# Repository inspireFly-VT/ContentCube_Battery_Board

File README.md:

View this project on [CADLAB.io](https://cadlab.io/project/28565). 

# battery_board
The battery and power management board for the PROVES Kit.
# Flight Heritage
| Version | Flights | Status |
| ----------- | ----------- | ----------- |
| V0 | Unflown | Not Supported |
| V1 | Unflown | Not Supported |
| V2 | Pleiades - Yearling, Pleaides - Squared | Supported |
| V3 | Planned Pleiades - Orpheus | In Development |
# Features
## battery_board_v2
The battery board flown on the Pleiades-Yearling and Pleiades-Squared missions. The board serves as an interface with the rest of the satellite. A 12 position picolock is utilized to interface between the Flight Controller and the Battery Board. The board interfaces with 5 solar faces of the satellite using 5 position picolocks. The other 2 position picolocks are used for interfacing with the inhibit scheme, battery heater, burn wire, and direct charging port. The hardware utilized on the module is the following:
- **LT3652 MPPT Solar Charger** is utilized to charge the batteries up from the solar faces. The Solar Charging circuitry should only allow higher potentials to be fed to the battery, and allow no reverse current into the charging circuitry.
- **PCA9685 LED Driver** is utilized to toggle the power to each of the solar faces. In the event that a sensor or other component fails on a face, it makes it possible to isolate the problem and power down the face.
- **TCA9548 I2C Multiplexer** is implemented to allow the use of a single I2C bus from the flight computer. This I2C bus can then get multiplexed to the solar faces. This allows the sensors on all of the faces to be the exact same, maintain the same addresses, and still be individually addressable. Two of the multiplexed lines are unused, 5 are used for each solar face, and 1 is used to breakout a stemma QT connection for additional sensors or I2C devices.
- **TPS54226PWP Switching Voltage Regulator** is utilized to maximize the efficiency of the system, and generate less heat central to the system. A 3.3V bus is created from the battery voltage and circuitry inspired by the PyCubed has been implemented to allow the satellite to reset the 3.3V bus. This functionality is known as the "One Shot" Regulator Reset that with a logic "High" applied, the 3.3V bus will shutdown and restart momentarily.
- **TPS7A4501 LDO Voltage Regulator** is implemented to supply 5V to the radio on the flight controller. This bus voltage can be toggled by an input taken from the flight controller.
- **(2) INA219 Power Monitors** are implemented to measure the power supplied from the solar cells, and the power dropped across the system. This data is fed back via the I2C bus to the flight controller
- **PTC2075 Temperature Sensor** is utilized to obtain ambient temperature readings from inside the satellite.
- **R5460N208AA** is utilized to disconnect the negative side of the batteries from the system in overcharge and overdischarge events.
- **APAN3109 Relay** is implemented to allow current to flow to the battery heater and burn wire MOSFETS.

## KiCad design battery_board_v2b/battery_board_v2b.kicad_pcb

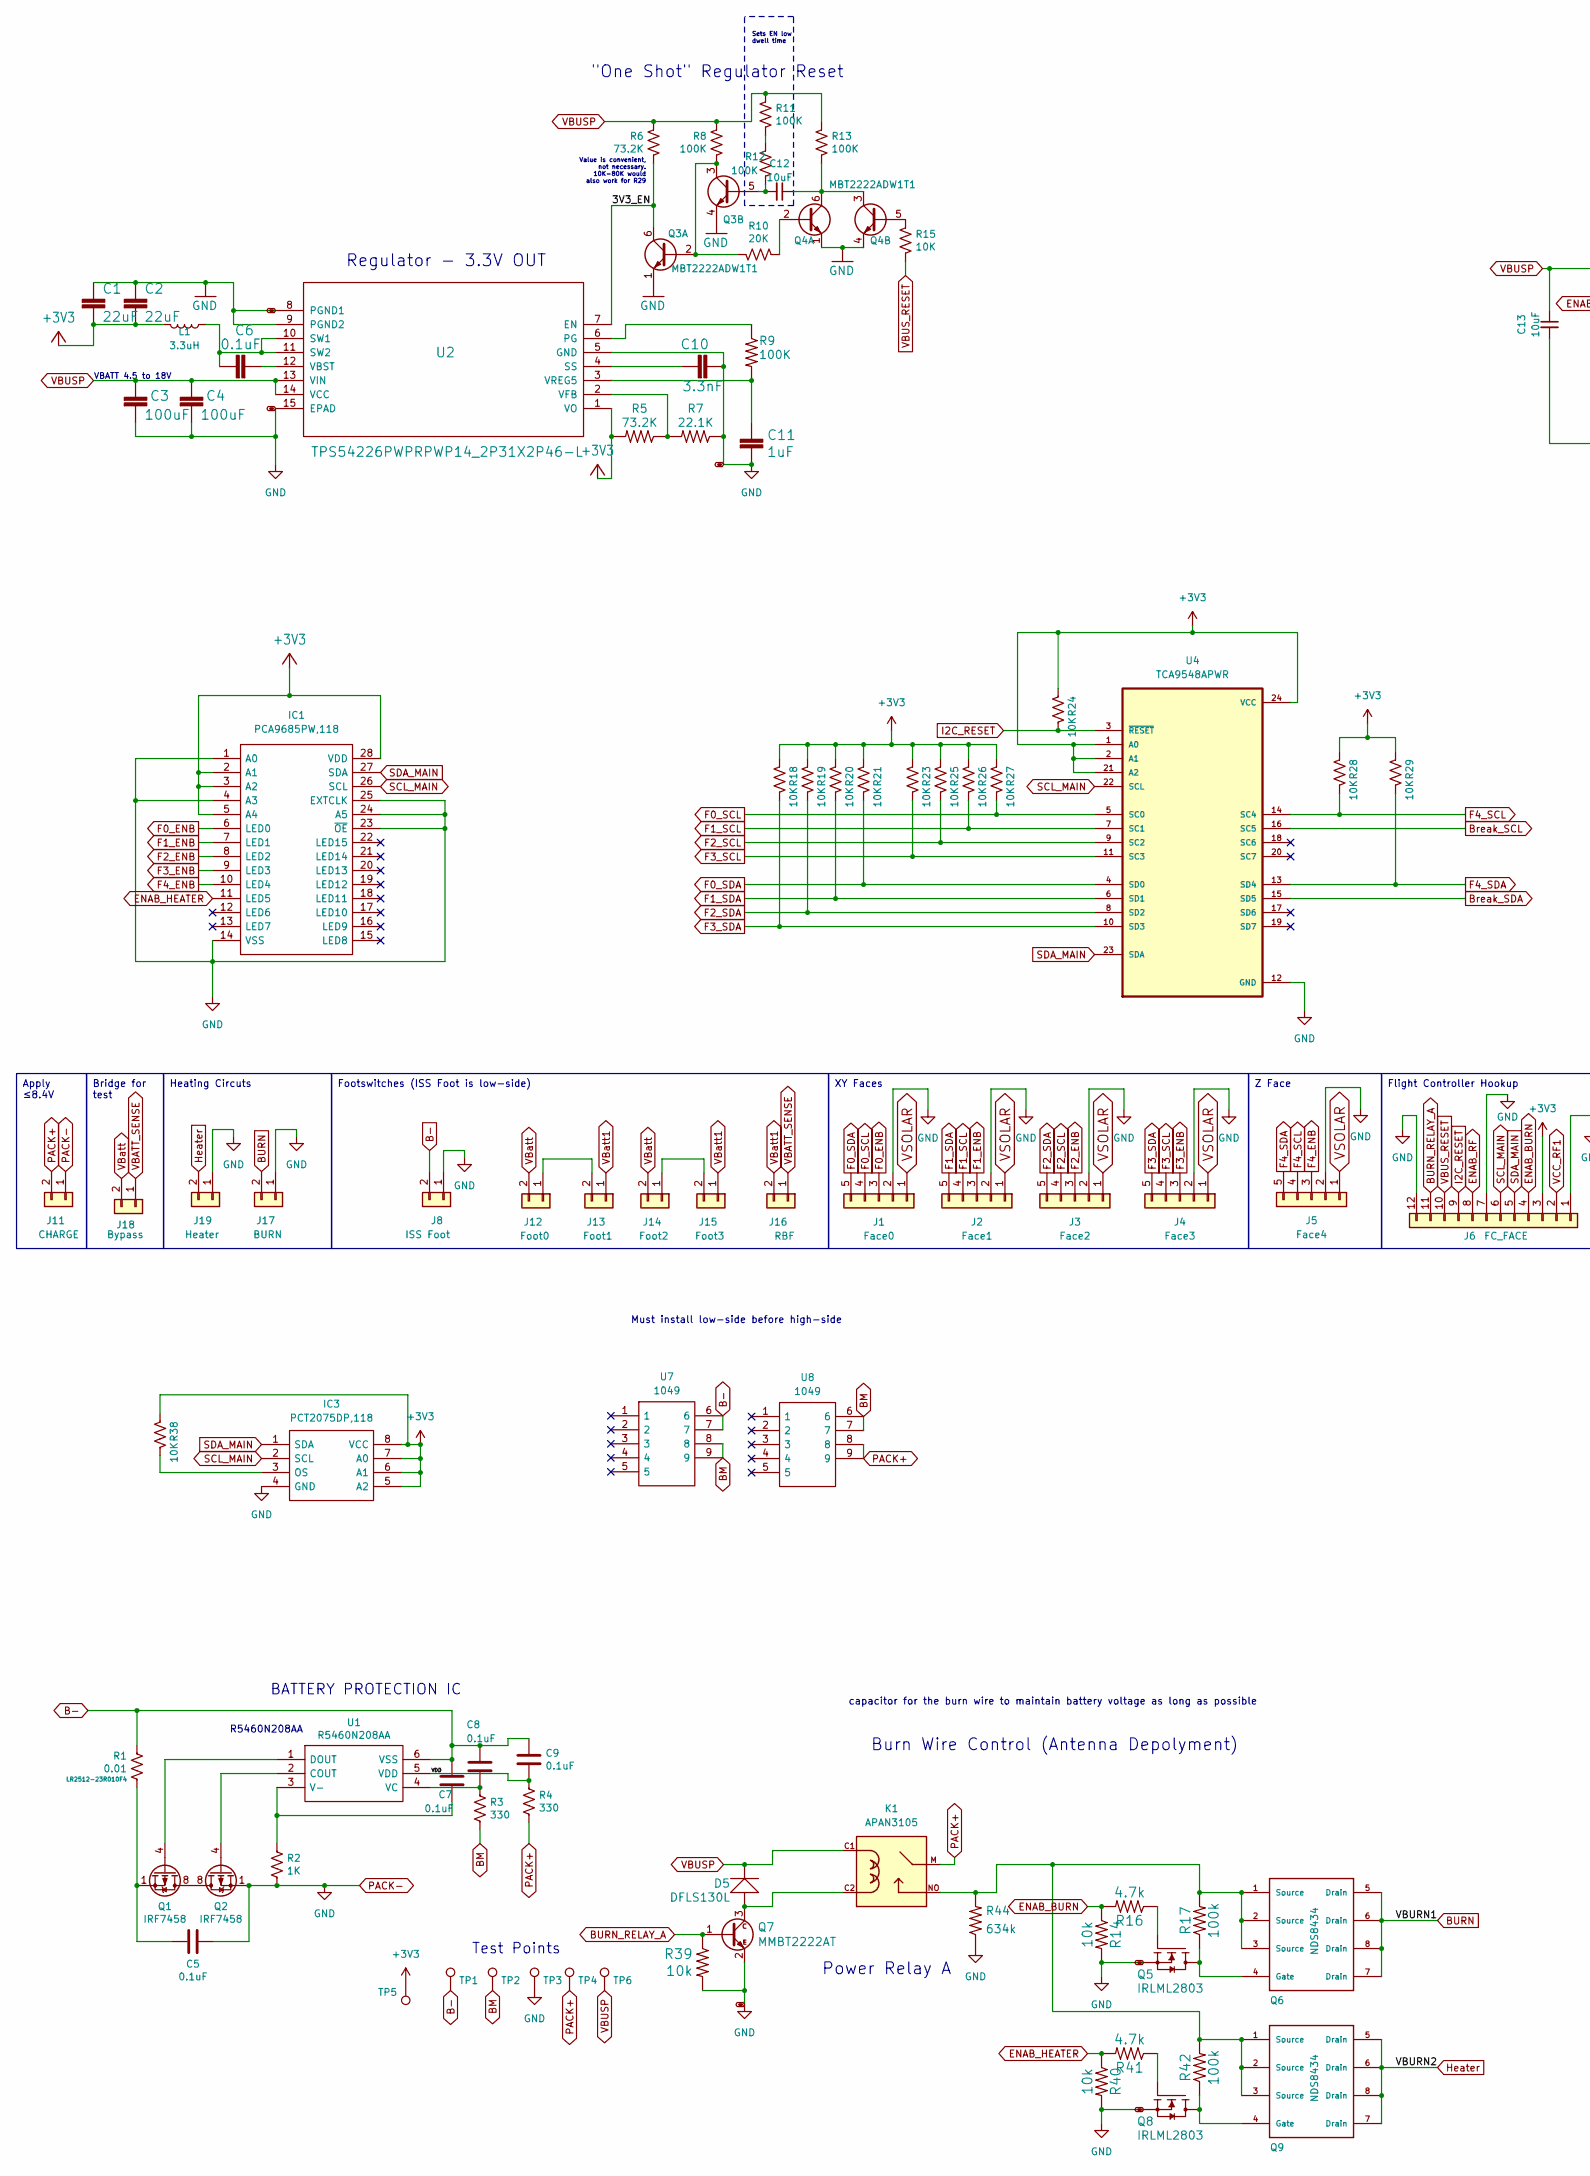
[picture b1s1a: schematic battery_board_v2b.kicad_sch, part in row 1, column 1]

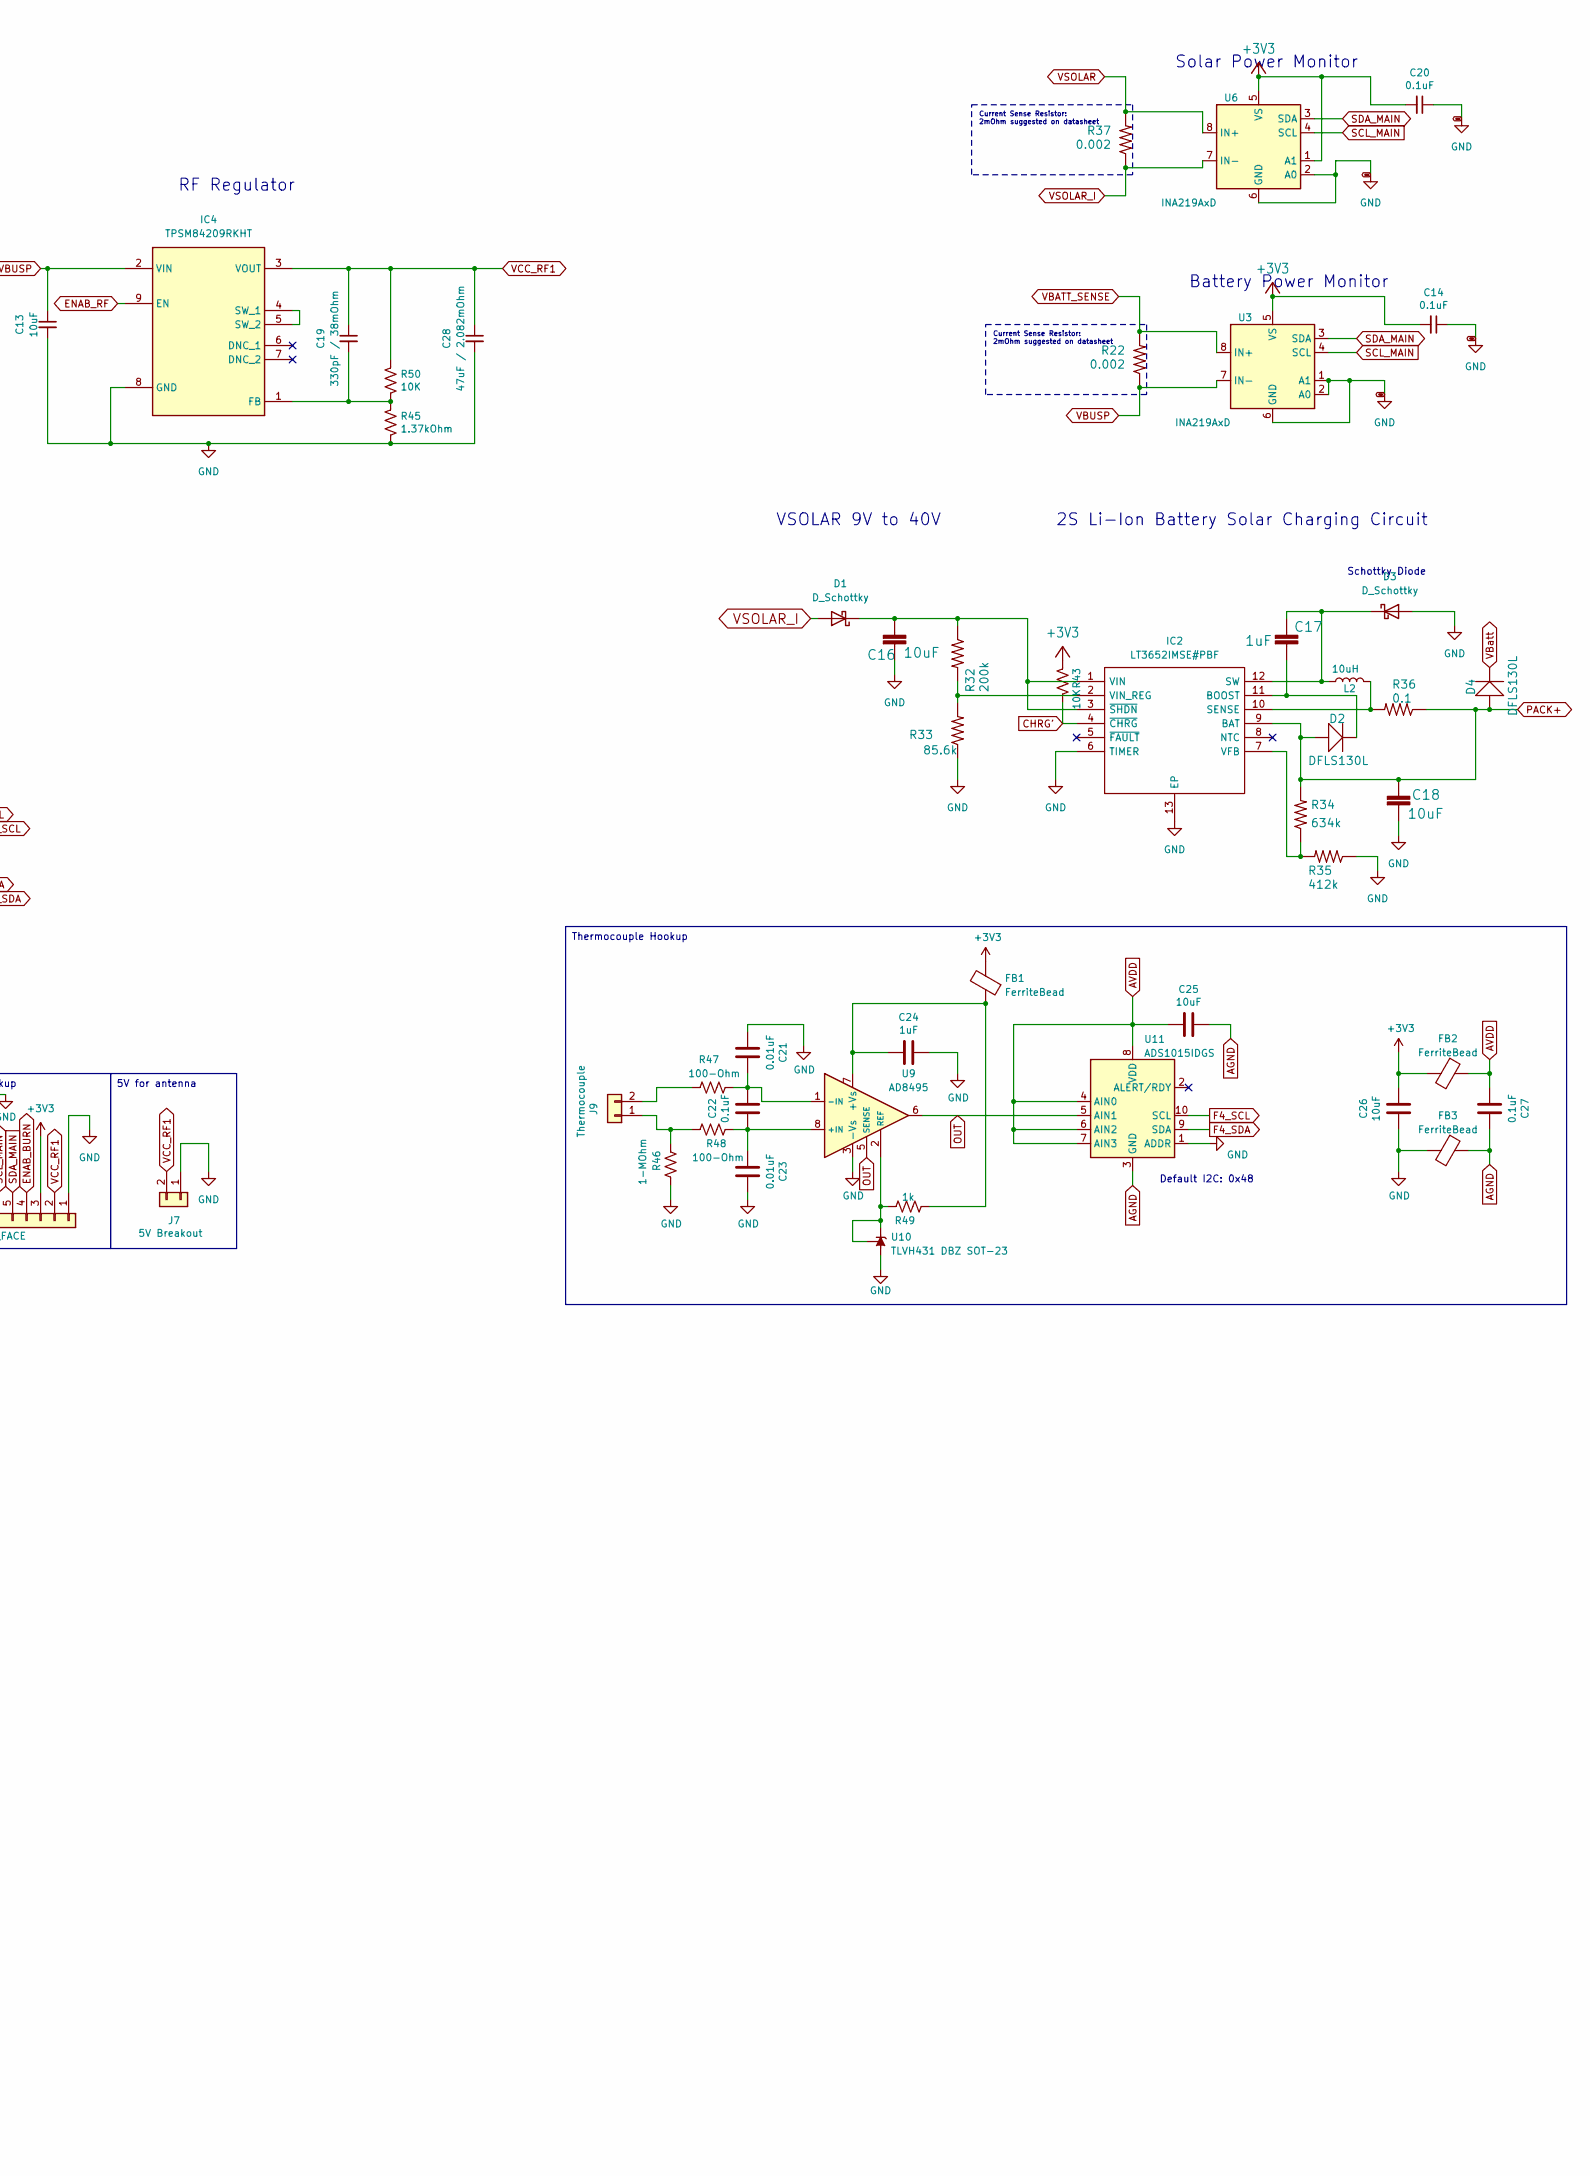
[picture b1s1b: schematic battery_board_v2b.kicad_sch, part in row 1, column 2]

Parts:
C1, C2: 22uF; C_0603_1608Metric
C3, C4: 100uF; C_1210_3225Metric
C5, C6, C7, C8, C9, C14, C20: 0.1uF; C_0603_1608Metric
C10: 3.3nF; C_0603_1608Metric
C11, C17: 1uF; C_0603_1608Metric
C12, C13, C16, C18: 10uF; C_0603_1608Metric
C19: 330pF / 38mOhm; C_0603_1608Metric
C21, C23: 0.01uF; C_0402_1005Metric_Pad0.74x0.62mm_HandSolder
C22, C27: 0.1uF; C_0402_1005Metric_Pad0.74x0.62mm_HandSolder
C24: 1uF; C_0402_1005Metric_Pad0.74x0.62mm_HandSolder
C25, C26: 10uF; C_0402_1005Metric_Pad0.74x0.62mm_HandSolder
C28: 47uF / 2.082mOhm; C_0603_1608Metric
D1, D3: D_Schottky; DIOM5226X262N
D2, D4, D5: DFLS130L; PWRDI-123; Manufacturer_Part_Number DFLS130L-7
FB1, FB2, FB3: FerriteBead; R_0603_1608Metric
IC1: PCA9685PW,118; SOP65P640X110-28N; Mouser Part Number 771-PCA9685PW,118
IC2: LT3652IMSE#PBF; SOP65P490X110-13N; Mouser Part Number 584-LT3652IMSE#PBF
IC3: PCT2075DP,118; TSSOP-8_3x3mm_P0.65mm; Mouser Part Number 771-PCT2075DP118
IC4: TPSM84209RKHT; Mouser Part Number 595-TPSM84209RKHT
J1: Face0; MOLEX_5040500591
J2: Face1; MOLEX_5040500591
J3: Face2; MOLEX_5040500591
J4: Face3; MOLEX_5040500591
J5: Face4; MOLEX_5040500591
J6: FC_FACE; Molex_Pico-Lock_504050-1291_1x12-1MP_P1.50mm_Horizontal
J7: 5V Breakout; MOLEX_504050-0291
J8: ISS Foot; MOLEX_504050-0291
J9: Thermocouple; MOLEX_504050-0291
J11: CHARGE; MOLEX_504050-0291
J12: Foot0; MOLEX_504050-0291
J13: Foot1; MOLEX_504050-0291
J14: Foot2; MOLEX_504050-0291
J15: Foot3; MOLEX_504050-0291
J16: RBF; MOLEX_504050-0291
J17: BURN; MOLEX_504050-0291
J18: Bypass; PinSocket_1x02_P2.54mm_Vertical
J19: Heater; MOLEX_504050-0291
K1: APAN3105; RELAY_APAN3105
L1: 3.3uH; L_1812_4532Metric; Manufacturer_Part_Number HPC5040NF-3R3MTH
L2: 10uH; L_1812_4532Metric; Manufacturer_Part_Number SNR5040K-330M
Q1, Q2: IRF7458; SOIC-8_3.9x4.9mm_P1.27mm
Q3, Q4: MBT2222ADW1T1; SOT-363_SC-70-6; Manufacturer_Part_Number MBT2222ADW1T1G
Q5, Q8: IRLML2803; SOT-23; Manufacturer_Part_Number MMBT2222AT
Q6, Q9: NDS8434; Manufacturer_Part_Number NDS8434
Q7: MMBT2222AT; SOT-523; Manufacturer_Part_Number MMBT2222ALT1G
R1: 0.01; R_2512_6332Metric
R2: 1K; R_0603_1608Metric
R3, R4: 330; R_0603_1608Metric
R5, R6: 73.2K; R_0603_1608Metric
R7: 22.1K; R_0603_1608Metric
R8, R9, R11, R12, R13: 100K; R_0603_1608Metric
R10: 20K; R_0603_1608Metric
R14, R39, R40: 10k; R_0603_1608Metric
R15, R18, R19, R20, R21, R23, R24, R25, R26, R27, R28, R29, R38, R43, R50: 10K; R_0603_1608Metric
R16, R41: 4.7k; R_0603_1608Metric
R17, R42: 100k; R_0603_1608Metric
R22, R37: 0.002; R_2512_6332Metric
R32: 200k; R_0603_1608Metric
R33: 85.6k; R_0603_1608Metric
R34, R44: 634k; R_0603_1608Metric
R35: 412k; R_0603_1608Metric
R36: 0.1; R_2512_6332Metric
R45: 1.37kOhm; R_0603_1608Metric
R46: 1-MOhm; R_0402_1005Metric_Pad0.72x0.64mm_HandSolder
R47, R48: 100-Ohm; R_0402_1005Metric_Pad0.72x0.64mm_HandSolder
R49: 1k; R_0402_1005Metric_Pad0.72x0.64mm_HandSolder
TP1, TP2, TP3, TP4, TP5, TP6: TestPoint; TestPoint_Loop_D1.80mm_Drill1.0mm_Beaded
U1: R5460N208AA; R5460N233AF-SOT95P280X130-6N; Manufacturer_Part_Number R5460N233AF-TR-FE; Mouser Part Number 848-R5460N233AFTRFE
U2: TPS54226PWPRPWP14_2P31X2P46-L; PWP14_2P31X2P46-L; Manufacturer_Part_Number TPS54226PWPR
U3, U6: INA219AxD; SOIC-8_3.9x4.9mm_P1.27mm
U4: TCA9548APWR; SOP65P640X120-24N
U7, U8: 1049; Mouser Part Number 534-1049
U9: AD8495; MSOP-8_3x3mm_P0.65mm
U10: TLVH431 DBZ SOT-23; SOT-23
U11: ADS1015IDGS; TSSOP-10_3x3mm_P0.5mm

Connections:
/3V3_EN: Q3.6 (C1), R6.2, U2.7 (EN)
/VDD: C9.2, R4.2, U1.5 (VDD)
AGND: C25.2, C27.2, FB3.1, U11.3 (GND)
AVDD: C25.1, C27.1, FB2.1, U11.4 (AIN0), U11.6 (AIN2), U11.7 (AIN3), U11.8 (VDD)
BM: R3.1, TP2.1, U7.8, U7.9, U8.6, U8.7
BURN: J17.2, Q6.5 (Drain), Q6.6 (Drain), Q6.7 (Drain), Q6.8 (Drain)
BURN_RELAY_A: J6.11, Q7.1 (B), R39.1
Break_SCL: U4.16 (SC5)
Break_SDA: U4.15 (SD5)
CHRG': IC2.4 (~CHRG), R43.2
ENAB_BURN: J6.4, R14.1, R16.2
ENAB_HEATER: IC1.11 (LED5), R40.1, R41.2
ENAB_RF: IC4.9 (EN), J6.8
F0_ENB: IC1.6 (LED0), J1.3
F0_SCL: J1.4, R27.2, U4.5 (SC0)
F0_SDA: J1.5, R21.2, U4.4 (SD0)
F1_ENB: IC1.7 (LED1), J2.3
F1_SCL: J2.4, R26.2, U4.7 (SC1)
F1_SDA: J2.5, R20.2, U4.6 (SD1)
F2_ENB: IC1.8 (LED2), J3.3
F2_SCL: J3.4, R25.2, U4.9 (SC2)
F2_SDA: J3.5, R19.2, U4.8 (SD2)
F3_ENB: IC1.9 (LED3), J4.3
F3_SCL: J4.4, R23.2, U4.11 (SC3)
F3_SDA: J4.5, R18.2, U4.10 (SD3)
F4_ENB: IC1.10 (LED4), J5.3
F4_SCL: J5.4, R28.2, U4.14 (SC4), U11.10 (SCL)
F4_SDA: J5.5, R29.2, U4.13 (SD4), U11.9 (SDA)
Heater: J19.2, Q9.5 (Drain), Q9.6 (Drain), Q9.7 (Drain), Q9.8 (Drain)
I2C_RESET: J6.9, R24.2, U4.3 (~RESET)
unnamed: C5.1, Q1.1 (S), Q1.2 (S), Q1.3 (S), R1.2
unnamed: C16.1, D1.1 (K), IC2.1 (VIN), IC2.3 (~SHDN), R32.1
unnamed: C17.1, D3.1 (K), IC2.12 (SW), L2.1
unnamed: C17.2, D2.C, IC2.11 (BOOST)
unnamed: IC2.10 (SENSE), L2.2, R36.2
unnamed: IC2.7 (VFB), R34.1, R35.2
unnamed: IC2.2 (VIN_REG), R32.2, R33.2
unnamed: IC3.3 (OS), R38.2
unnamed: C19.2, IC4.1 (FB), R45.1, R50.2
unnamed: IC4.4 (SW_1), IC4.5 (SW_2)
unnamed: J9.1, R46.1, R48.2
unnamed: J9.2, R47.1
unnamed: J12.1, J13.2
unnamed: J14.1, J15.2
unnamed: K1.NO, Q6.1 (Source), Q6.2 (Source), Q6.3 (Source), Q9.1 (Source), Q9.2 (Source), Q9.3 (Source), R17.2, R42.2, R44.2
unnamed: Q1.5 (D), Q1.6 (D), Q1.7 (D), Q1.8 (D), Q2.5 (D), Q2.6 (D), Q2.7 (D), Q2.8 (D)
unnamed: Q1.4 (G), U1.1 (DOUT)
unnamed: Q2.4 (G), U1.2 (COUT)
unnamed: Q3.2 (B1), Q3.3 (C2), R8.2, R10.2
unnamed: C12.2, Q3.5 (B2), R12.2
unnamed: Q4.2 (B1), R10.1
unnamed: C12.1, Q4.3 (C2), Q4.6 (C1), R13.2
unnamed: Q4.5 (B2), R15.1
unnamed: Q5.3 (D), Q6.4 (Gate), R17.1
unnamed: Q5.1 (G), R16.1
unnamed: D5.A, K1.C2, Q7.3 (C)
unnamed: Q8.3 (D), Q9.4 (Gate), R42.1
unnamed: Q8.1 (G), R41.1
unnamed: R11.2, R12.1
unnamed: C7.2, R2.1, U1.3 (V-)
unnamed: C8.2, R3.2, U1.4 (VC)
unnamed: R9.1, U2.6 (PG)
unnamed: C10.1, U2.4 (SS)
unnamed: C6.1, L1.1, U2.10 (SW1), U2.11 (SW2)
unnamed: C6.2, U2.12 (VBST)
unnamed: R5.1, R7.2, U2.2 (VFB)
unnamed: C11.1, R9.2, U2.3 (VREG5)
unnamed: C22.1, C23.1, R48.1, U9.8 (+IN)
unnamed: C24.1, FB1.1, R49.2, U9.7 (+Vs)
unnamed: C21.2, C22.2, R47.2, U9.1 (-IN)
unnamed: R49.1, U9.2 (REF), U10.1 (K), U10.2 (REF)
OUT: U9.5 (SENSE), U9.6, U11.5 (AIN1)
PACK+: C18.1, D2.A, D4.A, IC2.9 (BAT), J11.2, K1.M, R4.1, R34.2, R36.1, TP4.1, U8.8, U8.9
SCL_MAIN: IC1.26 (SCL), IC3.2 (SCL), J6.6, U3.4 (SCL), U4.22 (SCL), U6.4 (SCL)
SDA_MAIN: IC1.27 (SDA), IC3.1 (SDA), J6.5, U3.3 (SDA), U4.23 (SDA), U6.3 (SDA)
VBATT_SENSE: J16.1, J18.1, R22.2, U3.8 (IN+)
VBUSP: C3.1, C4.1, C13.1, D5.C, IC4.2 (VIN), K1.C1, R6.1, R8.1, R11.1, R13.1, R22.1, TP6.1, U2.13 (VIN), U2.14 (VCC), U3.7 (IN-)
VBUS_RESET: J6.10, R15.2
VBatt: D4.C, J12.2, J14.2, J18.2
VBatt1: J13.1, J15.1, J16.2
VCC_RF1: C19.1, C28.1, IC4.3 (VOUT), J6.2, J7.2, R50.1
VSOLAR: J1.1, J2.1, J3.1, J4.1, J5.1, R37.2, U6.8 (IN+)
VSOLAR_I: D1.2 (A), R37.1, U6.7 (IN-)

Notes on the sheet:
Thermocouple Hookup
XY Faces
Footswitches (ISS Foot is low-side)
Z Face
Heating Circuts
Apply ≤8.4V
Bridge for test
Flight Controller Hookup
5V for antenna
Must install low-side before high-side
Test Points
Current Sense Resistor: 2mOhm suggested on datasheet
"One Shot" Regulator Reset
VSOLAR 9V to 40V
Regulator - 3.3V OUT
Battery Power Monitor
Solar Power Monitor
Sets EN low dwell time
Default I2C: 0x48
BATTERY PROTECTION IC
2S Li-Ion Battery Solar Charging Circuit
R5460N208AA
Burn Wire Control (Antenna Depolyment)
Power Relay A
capacitor for the burn wire to maintain battery voltage as long as possible
Value is convenient, not necessary. 10K-80K would also work for R29
RF Regulator
Schottky Diode
VBATT 4.5 to 18V

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
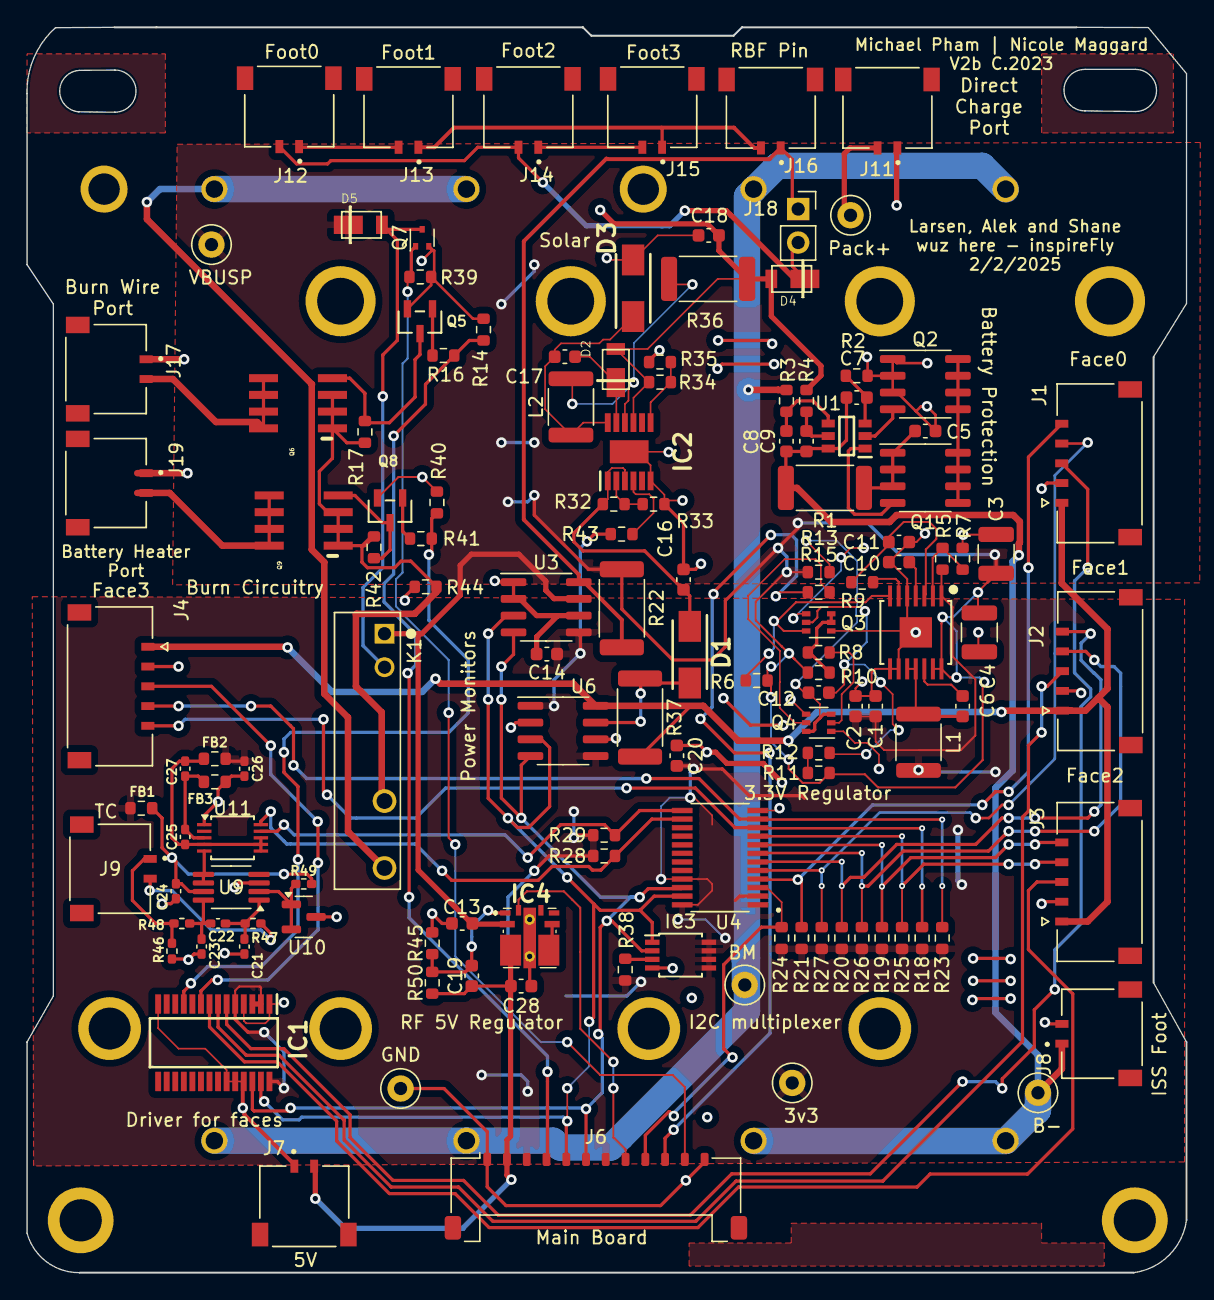
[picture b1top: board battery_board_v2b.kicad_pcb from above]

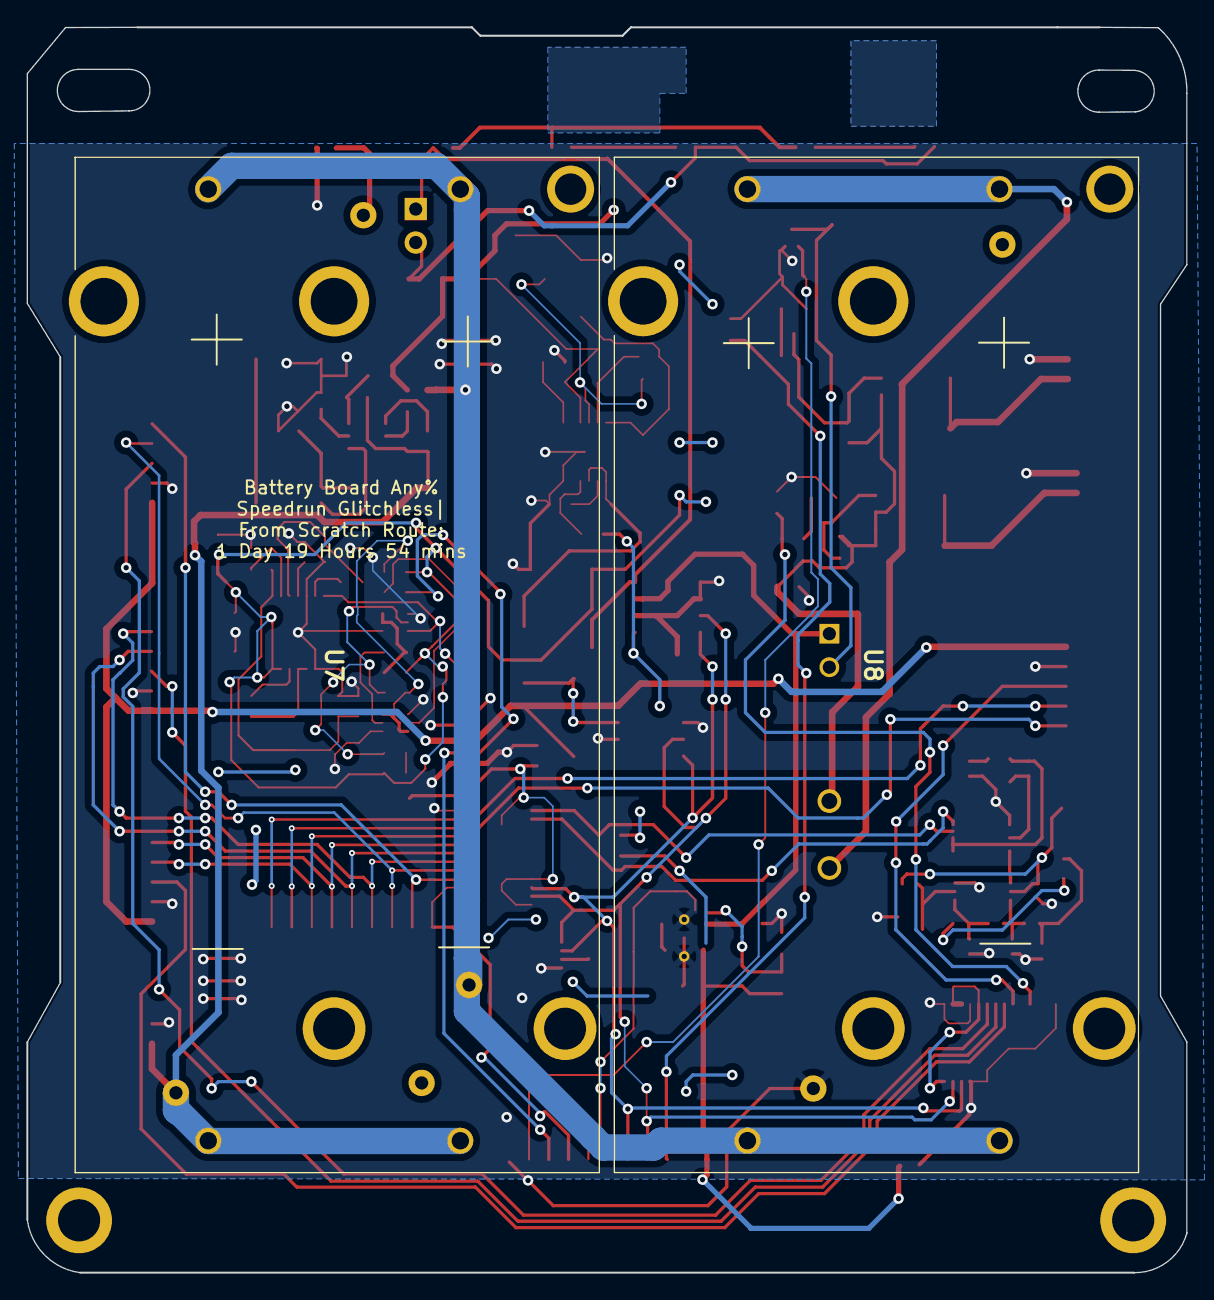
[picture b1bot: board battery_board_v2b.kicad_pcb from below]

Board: 4 copper layers, 88.0 x 94.5 mm, 132 parts (2 on the bottom side), 83 nets.

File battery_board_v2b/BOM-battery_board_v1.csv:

Id,Designator,Footprint,Quantity,Designation,Supplier and ref,Column1,_1
3,"C1,C2",C_0603_1608Metric,2,22uF,,,
31,C10,C_0603_1608Metric,1,3.3nF,C1613,,
4,"C16,C15,C18,C12",C_0603_1608Metric,4,10uF,C19702,,
8,"C17,C11",C_0603_1608Metric,2,1uF,C15849,,
43,"C19,C13",C_1210_3225Metric,2,200uF,C23742,,
60,"C22,C27",C_0402_1005Metric_Pad0.74x0.62mm_HandSolder,2,0.1uF,C60474,,
64,"C23,C21",C_0402_1005Metric_Pad0.74x0.62mm_HandSolder,2,0.01uF,C272878,,
48,C24,C_0402_1005Metric_Pad0.74x0.62mm_HandSolder,1,1uF,C77006,,
35,"C26,C25",C_0402_1005Metric_Pad0.74x0.62mm_HandSolder,2,10uF,C962136,,
33,"C3,C4",C_1210_3225Metric,2,100uF,,,
25,"C5,C6,C8,C9,C20,C7,C14",C_0603_1608Metric,7,0.1uF,C14663,,
71,"D3,D1",DIOM5226X262N,2,D_Schottky,C2892544,,
6,"D5,D2,D4",PWRDI-123,3,DFLS130L,C110493,,
12,"FB1,FB3,FB2",R_0603_1608Metric,3,FerriteBead,,,
73,IC1,SOP65P640X110-28N,1,"PCA9685PW,118",C2678753,,
65,IC2,SOP65P490X110-13N,1,LT3652IMSE#PBF,,,
70,IC3,TSSOP-8_3x3mm_P0.65mm,1,"PCT2075DP,118",C192518,,
56,J1,MOLEX_5040500591,1,Face0,,,
13,J11,MOLEX_504050-0291,1,CHARGE,,,
37,J12,MOLEX_504050-0291,1,Foot0,,,
34,J13,MOLEX_504050-0291,1,Foot1,,,
72,J14,MOLEX_504050-0291,1,Foot2,,,
17,J15,MOLEX_504050-0291,1,Foot3,,,
32,J16,MOLEX_504050-0291,1,RBF,,,
51,J17,MOLEX_504050-0291,1,BURN,,,
41,J18,PinSocket_1x02_P2.54mm_Vertical,1,Bypass,,,
18,J19,MOLEX_504050-0291,1,Heater,,,
62,J2,MOLEX_5040500591,1,Face1,,,
68,J3,MOLEX_5040500591,1,Face2,,,
15,J4,MOLEX_5040500591,1,Face3,,,
5,J6,Molex_Pico-Lock_504050-1291_1x12-1MP_P1.50mm_Horizontal,1,FC_FACE,,,
26,J7,MOLEX_504050-0291,1,5V Breakout,,,
54,J8,MOLEX_504050-0291,1,ISS,,,
57,J9,MOLEX_504050-0291,1,TC,,,
67,K1,RELAY_APAN3105,1,APAN3105,,,
58,L1,L_1812_4532Metric,1,3.3uH,C170174,,
59,L2,L_1812_4532Metric,1,10uH,,,
9,"Q2,Q1",SOIC-8_3.9x4.9mm_P1.27mm,2,IRF7458,C10879,,
11,"Q3,Q4",SOT-363_SC-70-6,2,MBT2222ADW1T1,C157366,,
30,"Q6,Q9",NDS8434,2,NDS8434,C2997,,
10,Q7,SOT-523,1,MMBT2222AT,,,
49,"Q8,Q5",SOT-23,2,IRLML2803,,,
52,R1,R_2512_6332Metric,1,0.01,,,
50,R10,R_0603_1608Metric,1,20K,C408766,,
2,"R14,R40,R39",R_0603_1608Metric,3,10k,C25804,,
20,R2,R_0603_1608Metric,1,1K,C21190,,
53,"R22,R37",R_2512_6332Metric,2,0.002,,,
16,R31,R_0603_1608Metric,1,3.3K,C22978,,
36,R32,R_0603_1608Metric,1,200k,C25811,,
28,R33,R_0603_1608Metric,1,85k,C227531,,
19,"R34,R44",R_0603_1608Metric,2,634k,C321970,,
74,R35,R_0603_1608Metric,1,412k,C321899,,
63,R36,R_2512_6332Metric,1,0.1,,,
46,"R4,R3",R_0603_1608Metric,2,330,C23138,,
7,"R41,R16",R_0603_1608Metric,2,4.7k,C23162,,
66,"R42,R17",R_0603_1608Metric,2,100k,,,
1,"R43,R28,R25,R29,R19,R21,R30,R26,R15,R20,R23,R18,R27,R38,R24",R_0603_1608Metric,15,10K,,,
24,R46,R_0402_1005Metric_Pad0.72x0.64mm_HandSolder,1,1-MOhm,,,
14,"R47,R48",R_0402_1005Metric_Pad0.72x0.64mm_HandSolder,2,100-Ohm,,,
47,R49,R_0402_1005Metric_Pad0.72x0.64mm_HandSolder,1,1k,,,
45,"R6,R5",R_0603_1608Metric,2,73.2K,C101180,,
39,R7,R_0603_1608Metric,1,22.1K,C139124,,
23,"R9,R8,R11,R12,R13",R_0603_1608Metric,5,100K,,,
44,U1,R5460N233AF-SOT95P280X130-6N,1,R5460N208AA,C259714,,
29,U10,SOT-23,1,TLVH431 DBZ SOT-23,,,
69,U11,TSSOP-10_3x3mm_P0.5mm,1,ADS1015IDGS,C1355858,,
40,U2,PWP14_2P31X2P46-L,1,TPS54226PWPRPWP14_2P31X2P46-L,,,
42,U4,SOP65P640X120-24N,1,TCA9548APWR,C130026,,
38,U5,TPS7A4501DCQT,1,TPS7A4501DCQT,,,
55,"U6,U3",SOIC-8_3.9x4.9mm_P1.27mm,2,INA219AxD,C138706,,
75,"U8,U7",1049,2,1049,,,
22,U9,MSOP-8_3x3mm_P0.65mm,1,AD8495,,,

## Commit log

2024-10-15 Add Custom Battery Board Add Custom Battery Board with 5v rail and ISS foot switch.
2024-10-15 Add Custom Battery Board inspireFly Custom battery board that has 5v output and ISS footswitch
2024-10-15 Backlink to CADLAB.io has been added.
2024-10-23 Updated to add thermocouple driver onboard
2024-10-23 Placed the thermocoupler circuitry on the board and modified schematic FOr the schematic I removed the adresse jumper ase we know which I2C adresse we are using.
2024-11-10 Updated for JLC Manufacturing
2024-11-10 Update .gitignore to add BOM files
2024-11-10 Added BOM Files
2024-11-10 Update BOM with part numbers and replace obsolete parts
2024-11-17 Updated BOM to reflect parts availability
2024-11-26 Updated BOM
2024-11-26 Fix Error
2024-11-26 Update BOM for final parts order
2025-02-03 Reliability Improvements
2025-02-03 Changed the 5V buck converter to a more efficient one
2025-02-03 Updated 5v reg and lowside switch
2025-02-03 Updated files for manufacturing
2025-02-06 Changed pinout for the fc connector
2025-02-07 Added part count
